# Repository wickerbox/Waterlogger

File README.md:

# Waterlogger Project

This project uses four water quality sensors from the <a href="https://github.com/OpenWaterProject/">OpenWaterProject</a> to text real-time turbidity, depth, conductivity, and temperature data from sewage outfall locations on the Willamette River in downtown Portland.

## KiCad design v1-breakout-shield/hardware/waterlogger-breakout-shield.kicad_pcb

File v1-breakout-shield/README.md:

# Waterlogger Project
## Sensor Shield v1.0

This is a simple breakout board to attach the sensors, the Fona 808 2G + GPS breakout board, and a microSD card to the Arduino Uno. 

It's intended to be a platform for prototyping the sensor suite at Portland Science Hackday on October 8th. The big questions to answer at the hackday are:

1. Can we deploy the sensors far below the cell-bearing water bottle? How far below?
1. Can we replicate the 5V-based circuits for turbidity, conductivity, temperature, and depth?
1. How to adapt the sensors to 3.7V of a 2500mAh LiPo battery?
1. How long does it take to charge the final unit?
1. Would a silicone stopper work instead of the bottle cap? How much does air pressure change affect the design? Is there a danger of it popping off? Silicone top would allow for extending the sensors. What about teh Presta valve idea? BlueRobotis Cable Penetrator.
1. How much does temperature change with depth in a river?

### Temperature Sensor Bill of Materials

|Part|Source|Link|
|----|------|----|
|10K Epoxy Thermistor|<a href="https://www.adafruit.com/products/372">Adafruit</a>|$4|
|1% 10K Resistor|Adafruit|Included|

### Conductivity Sensor Bill of Materials

|Part|Source|Link|
|----|------|----|
|Coqui sensor?|
|DIY Conductivity Sensor (Phillip Cook)|
|Nichrome 32AWG|Amazon|<a href="https://www.amazon.com/Pure-Atomist-Nichrome-Gauge-0-20mm/dp/B017E3PWIK/ref=sr_1_3?s=hi&ie=UTF8&qid=1475344249&sr=1-3&keywords=32+awg+nichrome">$6</a>|
|Concerns about 555 Timer under 1V|

### Depth Sensor Bill of Materials

|Part|Source|Link|
|----|------|----|
|555 Timer|
|1K|
|Twisted wires|
|Hot Glue or epoxy|

### Turbidity Sensor Bill of Materials

Try both 90-degree and pointing right at each other.

|Part|Source|Link|
|----|------|----|
|AD820 JFET Op Amp|
|SFH 213 Emitter|
|HIR204 Detector|
|(2) 1K Resistor|
|(1) 1M Resistor|
|(2) 100nF Capacitors|
|Acrylic Window 0.118" thick, 2" diameter|<a href="http://www.tapplastics.com/product/plastics/cake_circles/clear_acrylic_circles/140">Tap Plastics</a>|$1|/W                                                    
|Formazin (Hazardous!) for Calibration|<a href="http://www.hach.com/stablcal-turbidity-standard-100-ntu-100-ml/product?id=7640202637">Hach</a>|$48|

### Breakout Shield v1.0 Bill of Materials

|Part|Source|Link|
|----|------|----|
|Arduino Uno|Adafruit|<a href="https://www.adafruit.com/products/3033">$39.95</a>|
|Fona 808 2G + GPS Breakout Board|Adafruit|<a href="https://www.adafruit.com/products/2542">$49.95</a>|
|MicroSD Card holder|Digikey|<a href="http://www.digikey.com/product-detail/en/molex-llc/0475710001/WM9731CT-ND/4037907">$0.98</a>|
|1x16 0.1" pitch female header|Digikey|<a href="http://www.digikey.com/product-detail/en/sullins-connector-solutions/PPPC161LFBN-RC/S7049-ND/810188">$1.27</a>|

The printed board is a 2 layer board of 2.71x2.11 inches (69x53mm). $28.45 for three.

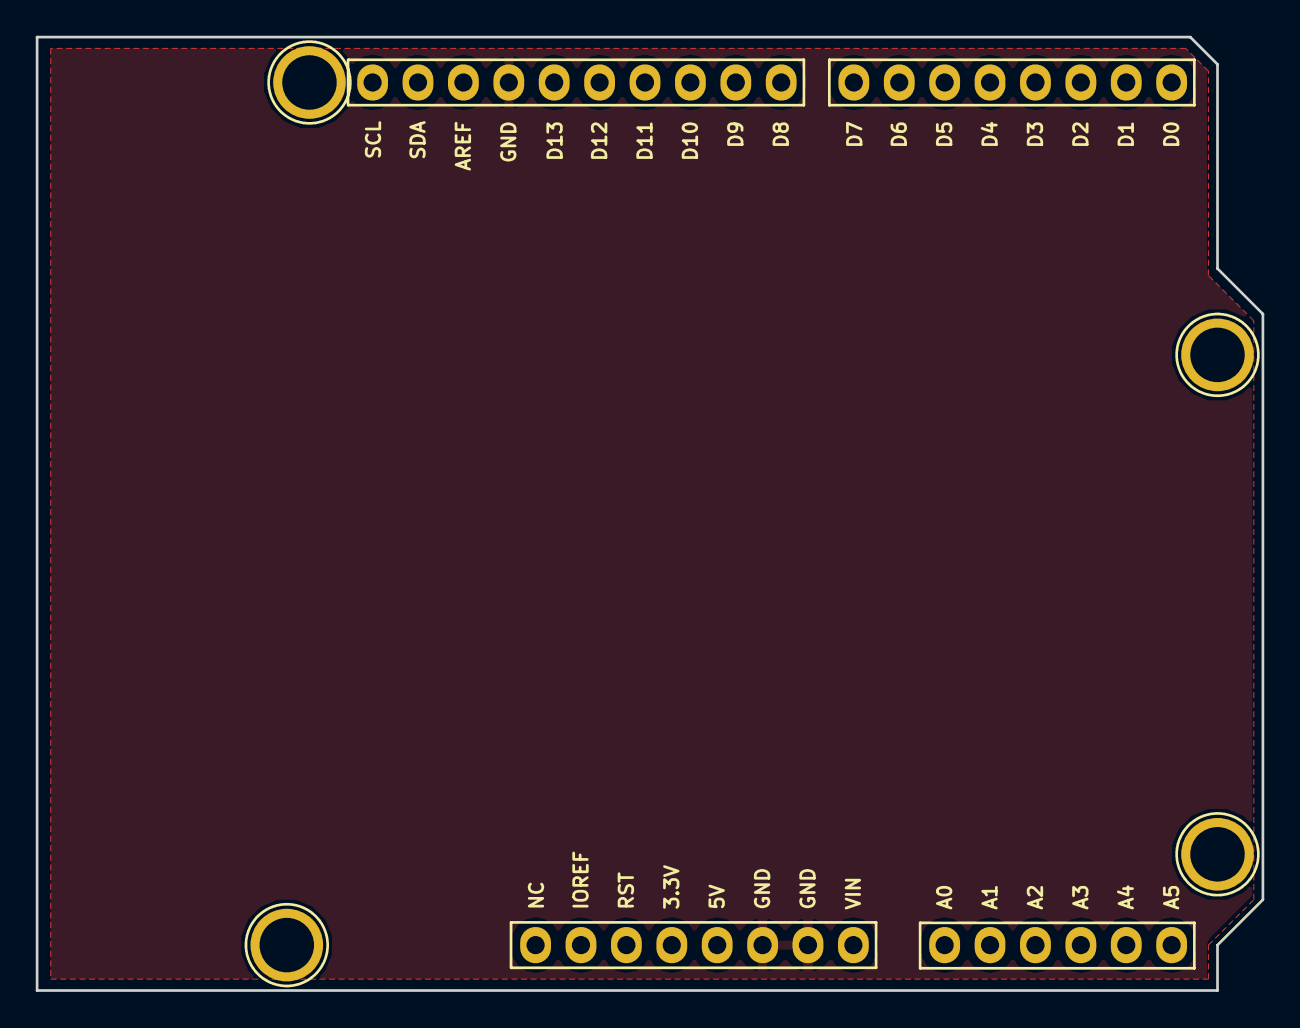
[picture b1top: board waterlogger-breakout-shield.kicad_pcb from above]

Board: 2 copper layers, 68.6 x 53.3 mm, 5 parts (0 on the bottom side), 4 nets, no tracks yet.

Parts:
U1, U2, U3, U4: HOLE; ARDUINO-MOUNTING-HOLE
U5: ARDUINO-101-SHIELD

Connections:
+5V: U5.5V, U5.AREF
/A4: U5.A4, U5.SDA
/A5: U5.A5, U5.SCL
GND: U5.GND1, U5.GND2, U5.GND3

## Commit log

2016-10-08 Update.
2016-10-16 Decided on sensor breakout shield as first step.
2016-10-16 Added the sensor circuits as they appear on my breadboard.

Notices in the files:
v1-breakout-shield/hardware/waterlogger-breakout-shield.kicad_pcb:
Released under the CERN Open Hardware License v1.2
